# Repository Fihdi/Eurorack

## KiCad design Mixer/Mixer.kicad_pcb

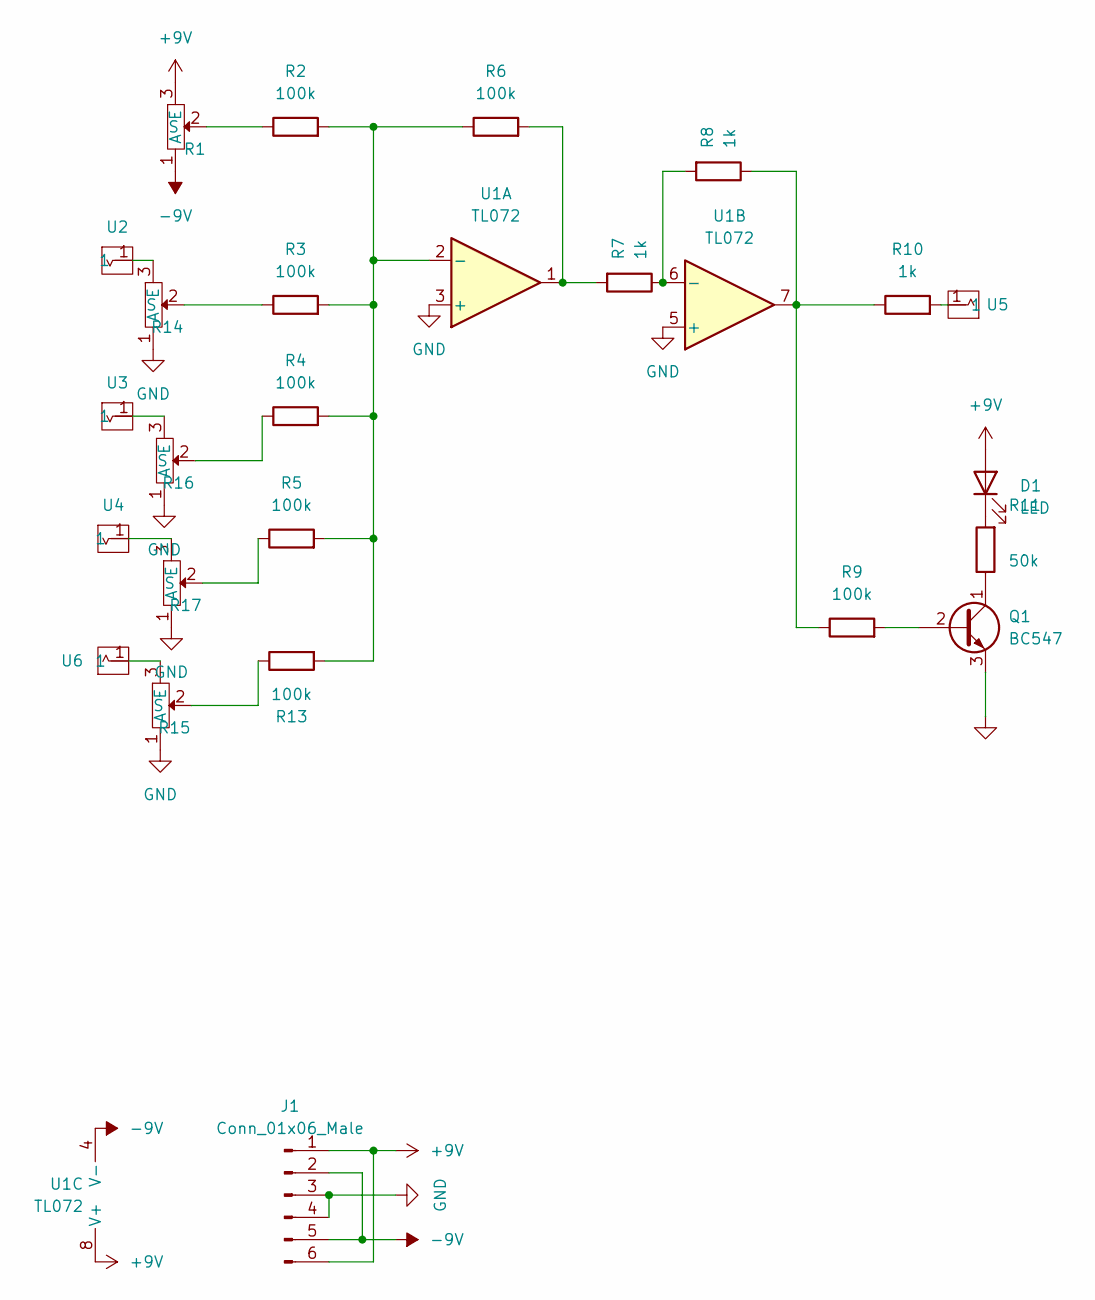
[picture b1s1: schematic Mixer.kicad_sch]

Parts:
D1: LED; LED_D5.0mm
J1: Conn_01x06_Male; PinHeader_1x06_P2.54mm_Vertical
Q1: BC547; TO-92_Inline_Wide
R1, R14, R15, R16, R17: AlpsPot
R2, R3, R4, R5, R6, R9, R13: 100k; R_Axial_DIN0204_L3.6mm_D1.6mm_P7.62mm_Horizontal
R7, R8, R10: 1k; R_Axial_DIN0204_L3.6mm_D1.6mm_P7.62mm_Horizontal
R11: 50k; R_Axial_DIN0204_L3.6mm_D1.6mm_P7.62mm_Horizontal
U1: TL072; DIP-8_W7.62mm
U2, U3, U4, U5, U6: Aux_flush; 3mm5 Mono Aux

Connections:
+9V: D1.2 (A), J1.1, J1.6, R1.3 (E), U1.8 (V+)
-9V: J1.2, J1.5, R1.1 (A), U1.4 (V-)
GND: J1.3, J1.4, Q1.3 (E), R14.1 (A), R15.1 (A), R16.1 (A), R17.1 (A), U1.3 (+), U1.5 (+)
unnamed: D1.1 (K), R11.2
unnamed: Q1.2 (B), R9.2
unnamed: Q1.1 (C), R11.1
unnamed: R1.2 (S), R2.1
unnamed: R6.2, R7.2, U1.1
unnamed: R8.1, R9.1, R10.1, U1.7
unnamed: R10.2, U5.1
unnamed: R14.3 (E), U2.1
unnamed: R3.1, R14.2 (S)
unnamed: R15.3 (E), U6.1
unnamed: R13.1, R15.2 (S)
unnamed: R16.3 (E), U3.1
unnamed: R4.1, R16.2 (S)
unnamed: R17.3 (E), U4.1
unnamed: R5.1, R17.2 (S)
unnamed: R2.2, R3.2, R4.2, R5.2, R6.1, R13.2, U1.2 (-)
unnamed: R7.1, R8.2, U1.6 (-)

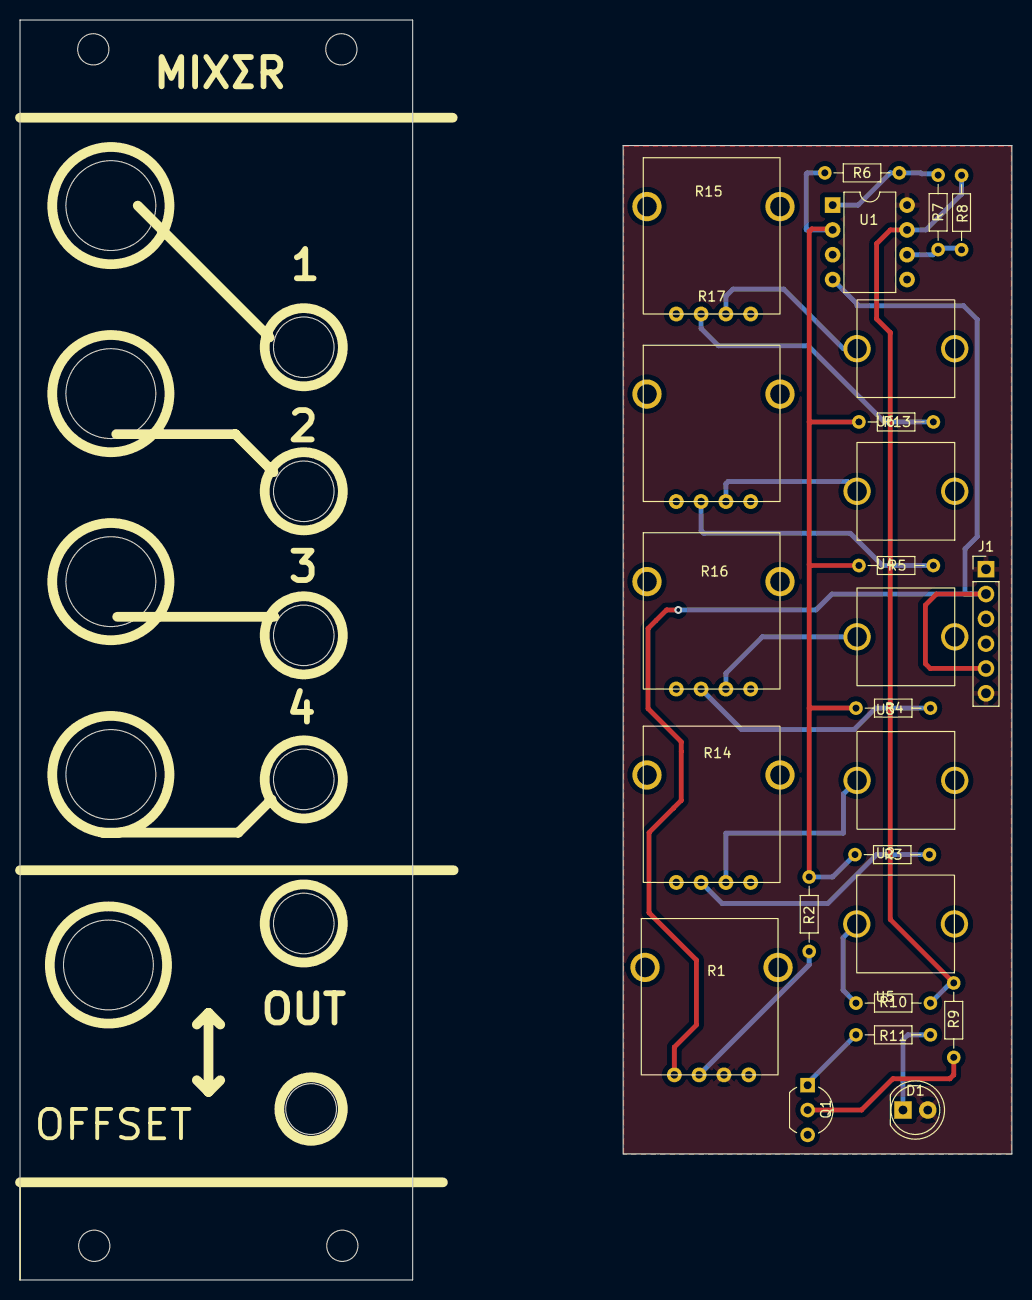
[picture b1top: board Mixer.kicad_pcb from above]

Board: 2 copper layers, 39.8 x 103.2 mm, 25 parts (0 on the bottom side), 20 nets.

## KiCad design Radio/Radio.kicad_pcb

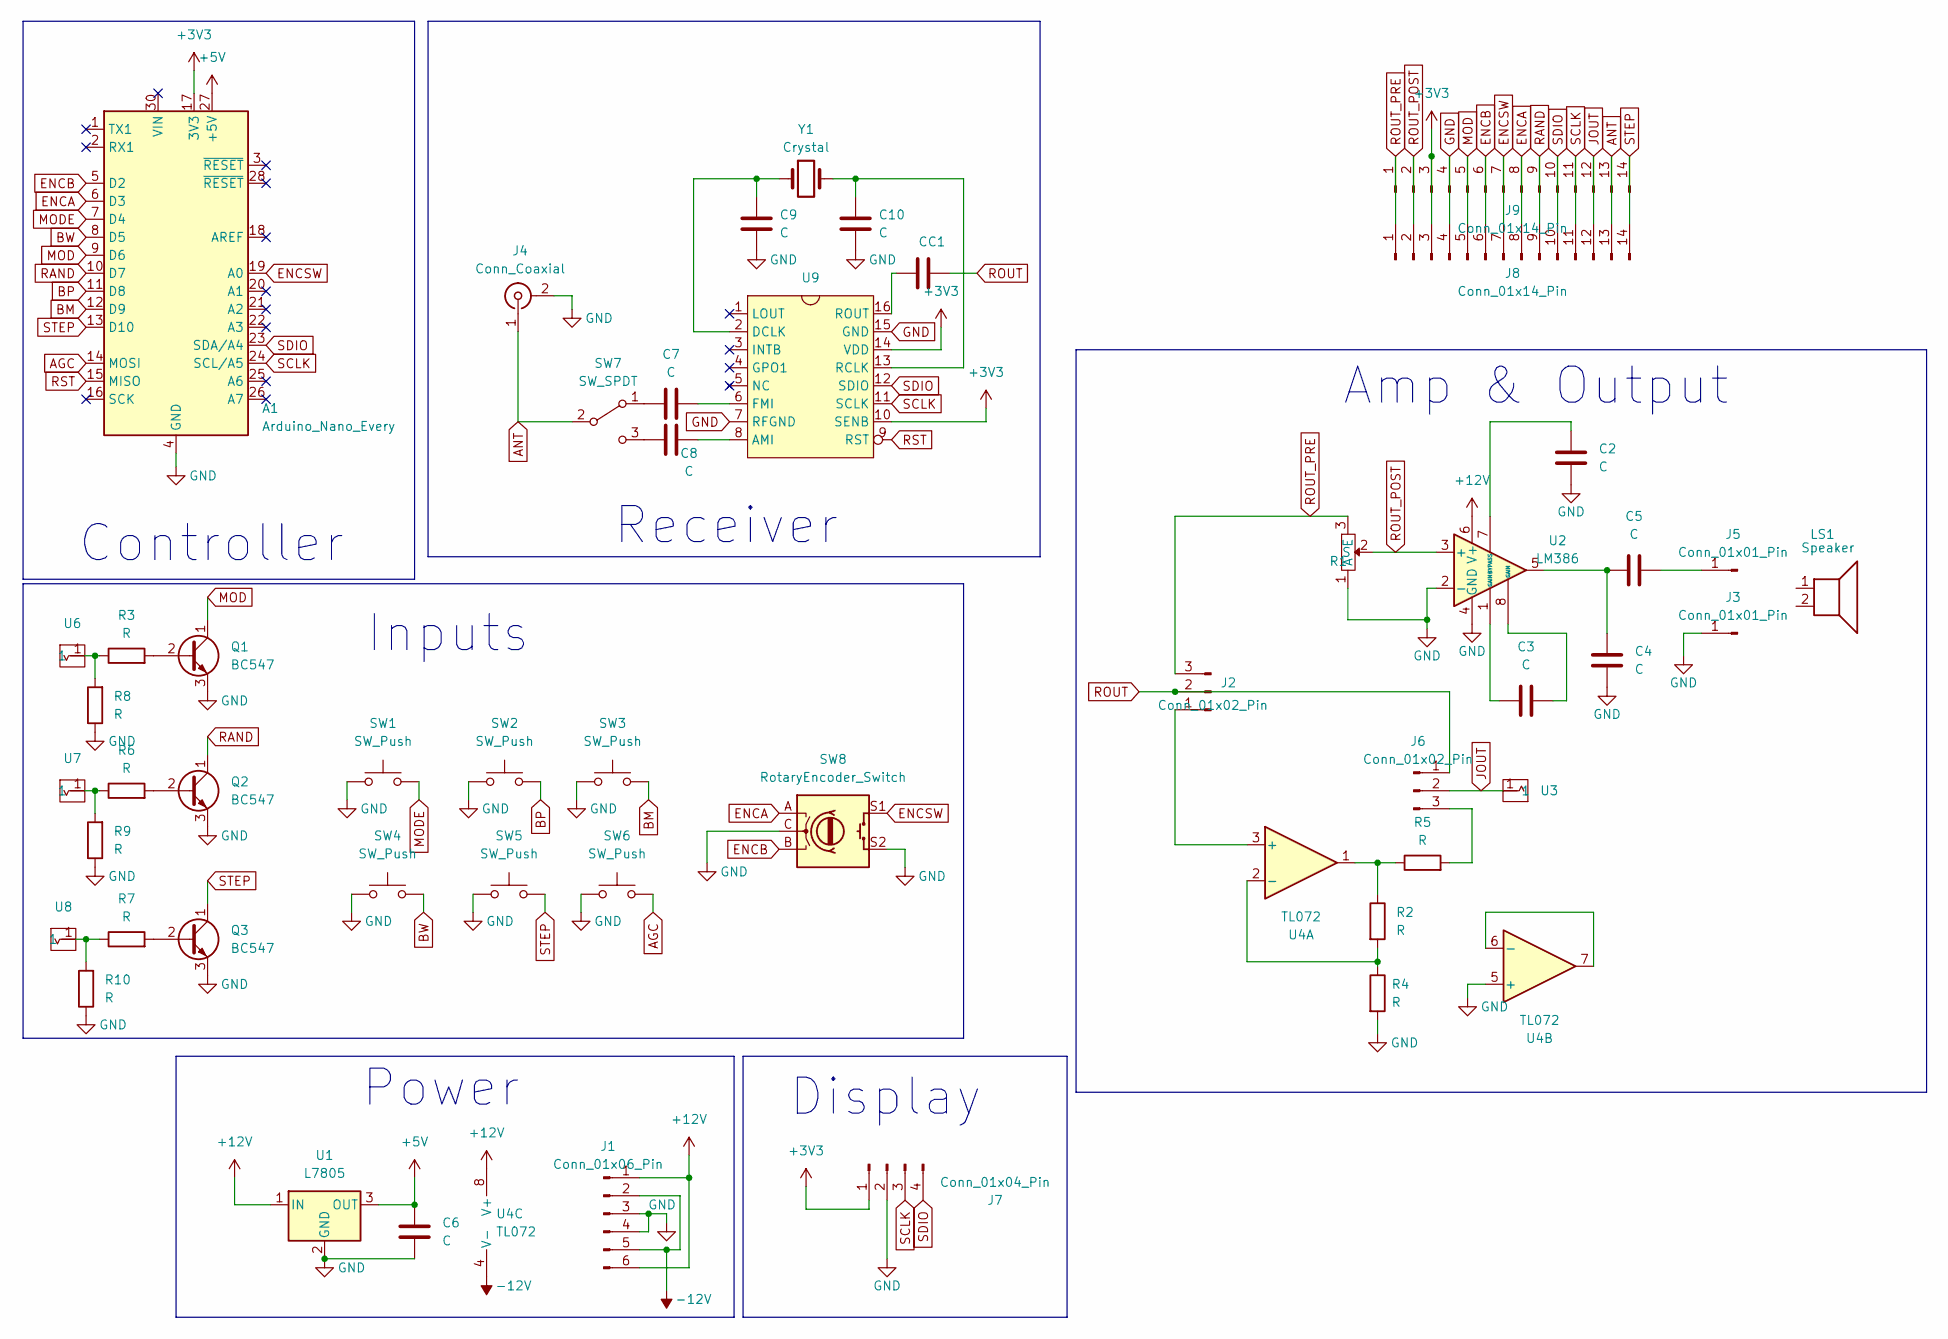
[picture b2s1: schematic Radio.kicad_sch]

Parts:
A1: Arduino_Nano_Every; Arduino_Nano
C1, C2, C3, C4, C5, C6, C7, C8, C9, C10: C; C_Rect_L9.0mm_W2.5mm_P7.50mm_MKT
J1: Conn_01x06_Pin; PinHeader_1x06_P2.54mm_Vertical
J2, J6: Conn_01x02_Pin; PinHeader_1x03_P2.54mm_Vertical
J3, J5: Conn_01x01_Pin; PinSocket_1x01_P2.54mm_Vertical
J4: Conn_Coaxial; BNC_TEConnectivity_1478035_Horizontal
J7: Conn_01x04_Pin; PinSocket_1x04_P2.54mm_Vertical
J8: Conn_01x14_Pin; PinHeader_1x14_P2.54mm_Vertical
J9: Conn_01x14_Pin; PinSocket_1x14_P2.54mm_Vertical
LS1: Speaker
Q1, Q2, Q3: BC547; TO-92_Inline
R1: AlpsPot
R2, R3, R4, R5, R6, R7, R8, R9, R10: R; R_Axial_DIN0204_L3.6mm_D1.6mm_P7.62mm_Horizontal
SW1, SW2, SW3, SW4, SW5, SW6: SW_Push; PinSocket_1x02_P2.54mm_Vertical
SW7: SW_SPDT
SW8: RotaryEncoder_Switch; RotaryEncoder_Alps_EC11E-Switch_Vertical_H20mm
U1: L7805; TO-220-3_Vertical
U2: LM386; DIP-8_W7.62mm
U3, U6, U7, U8: Aux_flush; aux_flush
U4: TL072; DIP-8_W7.62mm
U9: SOIC-16_4.55x10.3mm_P1.27mm
Y1: Crystal; Crystal_DS26_D2.0mm_L6.0mm_Vertical

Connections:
+3V3: A1.17 (3V3), J7.1, J8.3, J9.3, U9.10 (SENB), U9.14 (VDD)
+5V: A1.27 (+5V), C6.1, U1.3 (OUT)
+12V: J1.1, J1.6, U1.1 (IN), U2.6 (V+), U4.8 (V+)
-12V: J1.2, J1.5, U4.4 (V-)
AGC: A1.14 (MOSI), SW6.2
ANT: J4.1 (In), J8.13, J9.13, SW7.2 (B); also elsewhere on the board
BM: A1.12 (D9), SW3.2
BP: A1.11 (D8), SW2.2
BW: A1.8 (D5), SW4.2
ENCA: A1.6 (D3), J8.8, J9.8, SW8.A
ENCB: A1.5 (D2), J8.6, J9.6, SW8.B
ENCSW: A1.19 (A0), J8.7, J9.7, SW8.S1
GND: A1.4 (GND), A1.29 (GND), C2.1, C4.1, C6.2, C9.2, C10.2, J1.3, J1.4, J3.1, J4.2 (Ext), J7.2, J8.4, J9.4, Q1.3 (E), Q2.3 (E), Q3.3 (E), R1.1 (A), R4.2, R8.1, R9.1, R10.1, SW1.1, SW2.1, SW3.1, SW4.1, SW5.1, SW6.1, SW8.C, SW8.S2, U1.2 (GND), U2.2 (-), U2.4 (GND), U4.5 (+), U9.7 (RFGND), U9.15 (GND)
JOUT: J6.2, J8.12, J9.12, U3.1
MOD: A1.9 (D6), J8.5, J9.5, Q1.1 (C)
MODE: A1.7 (D4), SW1.2
unnamed: C3.1, U2.8 (GAIN)
unnamed: C3.2, U2.1 (GAIN)
unnamed: C4.2, C5.2, U2.5
unnamed 19: C7.2, SW7.1 (A); also elsewhere on the board
unnamed 20: C8.2, SW7.3 (C); also elsewhere on the board
unnamed: J2.1, U4.3 (+)
unnamed: C5.1, J5.1
unnamed: J6.3, R5.2
unnamed: Q1.2 (B), R3.2
unnamed: Q2.2 (B), R6.2
unnamed: Q3.2 (B), R7.2
unnamed: R2.1, R5.1, U4.1
unnamed: R3.1, R8.2, U6.1
unnamed: R6.1, R9.2, U7.1
unnamed: R7.1, R10.2, U8.1
unnamed: C2.2, U2.7 (BYPASS)
unnamed: R2.2, R4.1, U4.2 (-)
unnamed: U4.6 (-), U4.7
unnamed: C8.1, U9.8 (AMI)
unnamed: C9.1, U9.2 (DCLK), Y1.1
unnamed: C7.1, U9.6 (FMI)
unnamed: C10.1, U9.13 (RCLK), Y1.2
unnamed: C1.1, U9.16 (ROUT)
RAND: A1.10 (D7), J8.9, J9.9, Q2.1 (C)
ROUT: C1.2, J2.2, J6.1
ROUT_POST: J8.2, J9.2, R1.2 (S), U2.3 (+)
ROUT_PRE: J2.3, J8.1, J9.1, R1.3 (E)
RST: A1.15 (MISO), U9.9 (RST)
SCLK: A1.24 (SCL/A5), J7.3, J8.11, J9.11, U9.11 (SCLK)
SDIO: A1.23 (SDA/A4), J7.4, J8.10, J9.10, U9.12 (SDIO)
STEP: A1.13 (D10), J8.14, J9.14, Q3.1 (C), SW5.2

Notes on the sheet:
Amp & Output
Controller
Power
Display
Inputs
Receiver

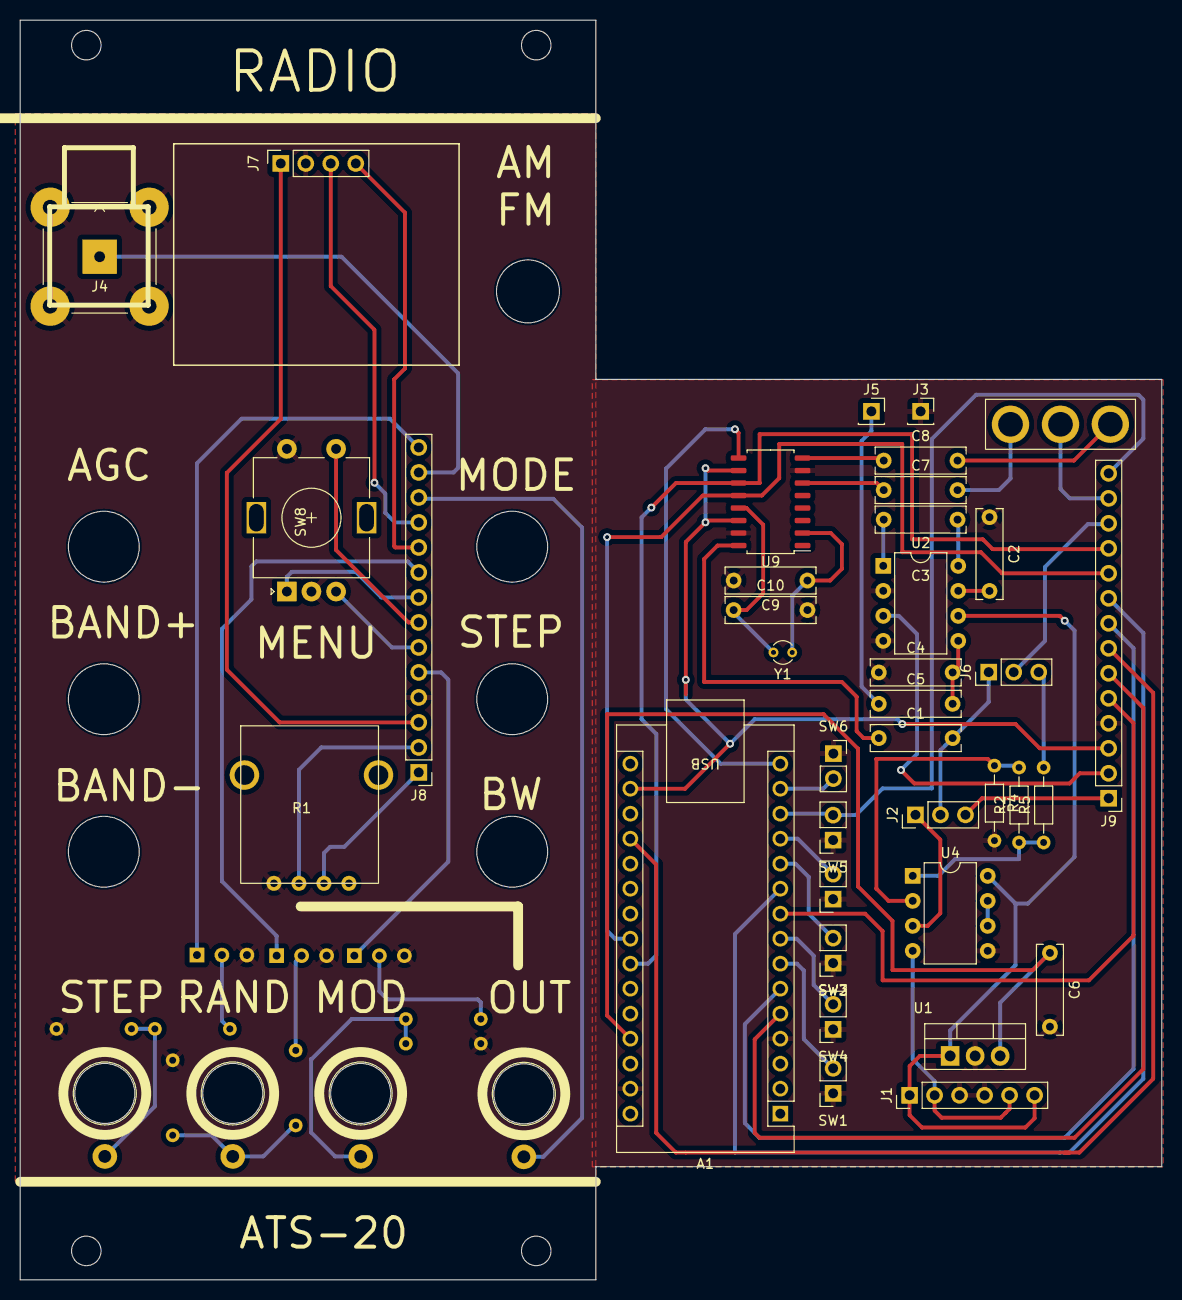
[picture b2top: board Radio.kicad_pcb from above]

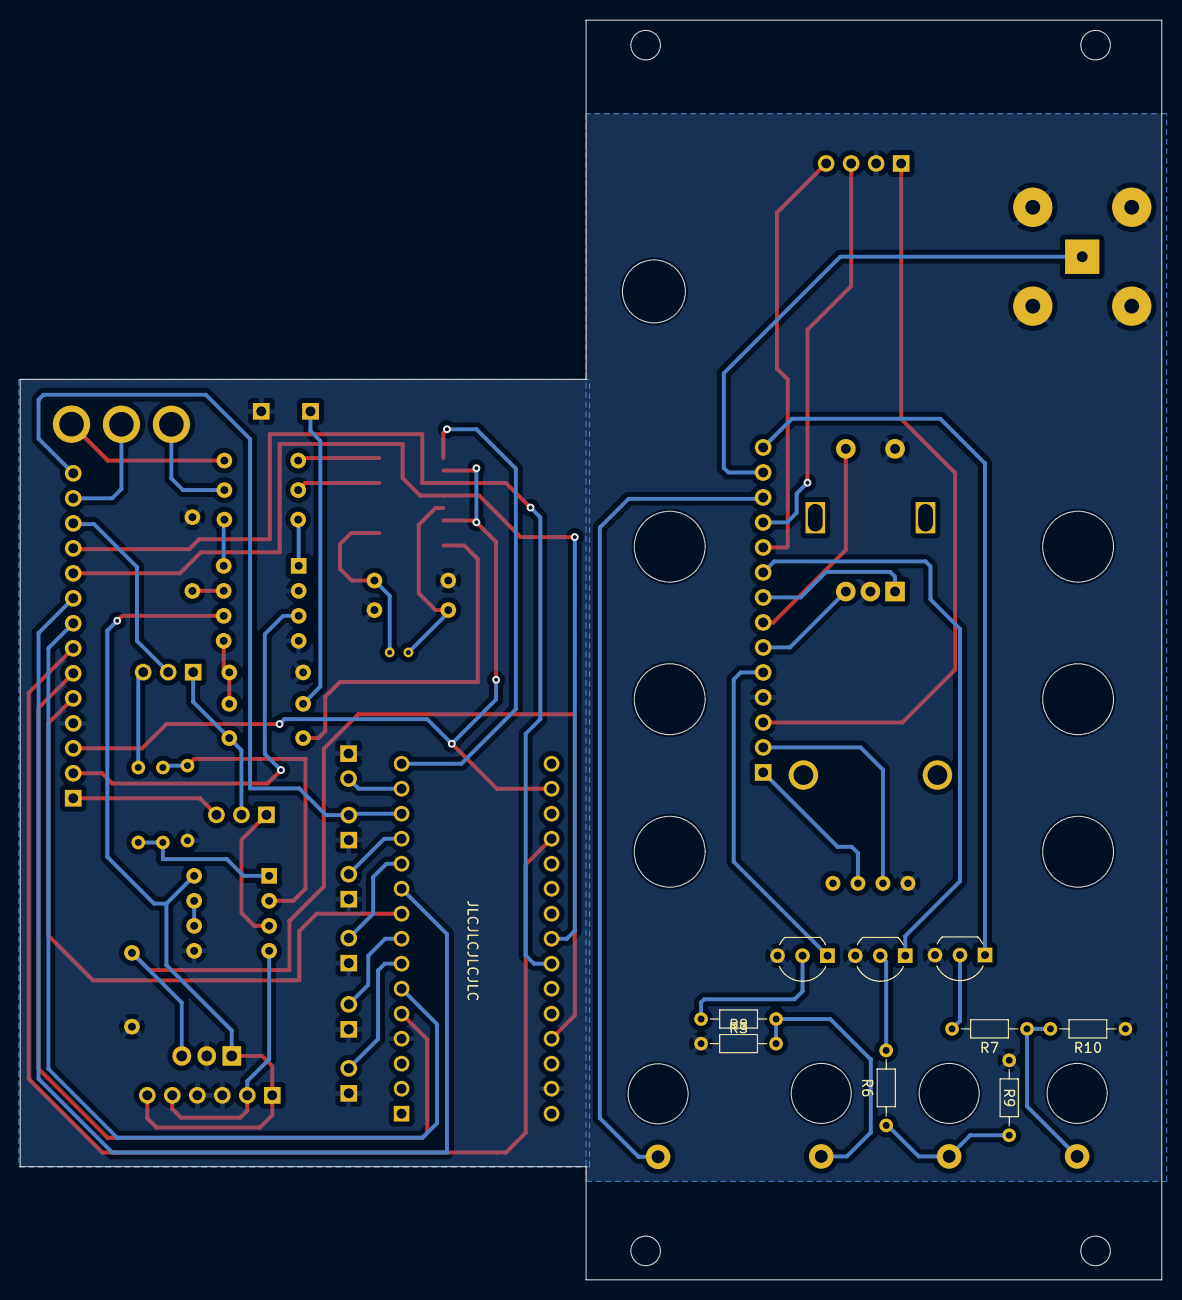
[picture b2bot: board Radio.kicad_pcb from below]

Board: 2 copper layers, 116.0 x 128.0 mm, 50 parts (9 on the bottom side), 47 nets.

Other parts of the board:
U5: Switch

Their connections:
ANT: U5.2; also elsewhere on the board
unnamed 19: U5.1; also elsewhere on the board
unnamed 20: U5.3; also elsewhere on the board

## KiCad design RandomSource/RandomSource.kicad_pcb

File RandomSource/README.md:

# 10hp Sample and Hold / Random Voltage generator 

Improved Version of SAH-TAH, contains a noise generator, sample and hold, burst, slew and bounce circuit. Signal routing is done via switches.  

At its core SAH-TAH has two core components: a noise generator and sample/track and hold. Random also has the same core, but with two extra features, a comparator and a slewing circuit.

SAH/TAH changes the SAH output from sample and hold to track and hold.

The comparator has a reference voltage that can be set with the REF knob. The input to the comparator can be set as NOISE or SAH. When the input signal to the comparator is less than the reference voltage, GATES will output 10V. This can be used to output random gates. BURST doesnt seems to work.

SLEW increases the time it takes for the SLEW OUT output to catch up to the SAH output by varying the RC time constant. The BOUNCE knob adds a delay to the feedback signal with a second RC circuit, causing the SAH SLEW output to over- and undershoot the sampled valued. The MODE switch can select between the first and second RC circuit. This can be used to output smooth random or chaotic random voltages when set to IN/NOISE switch is set to NOISE.

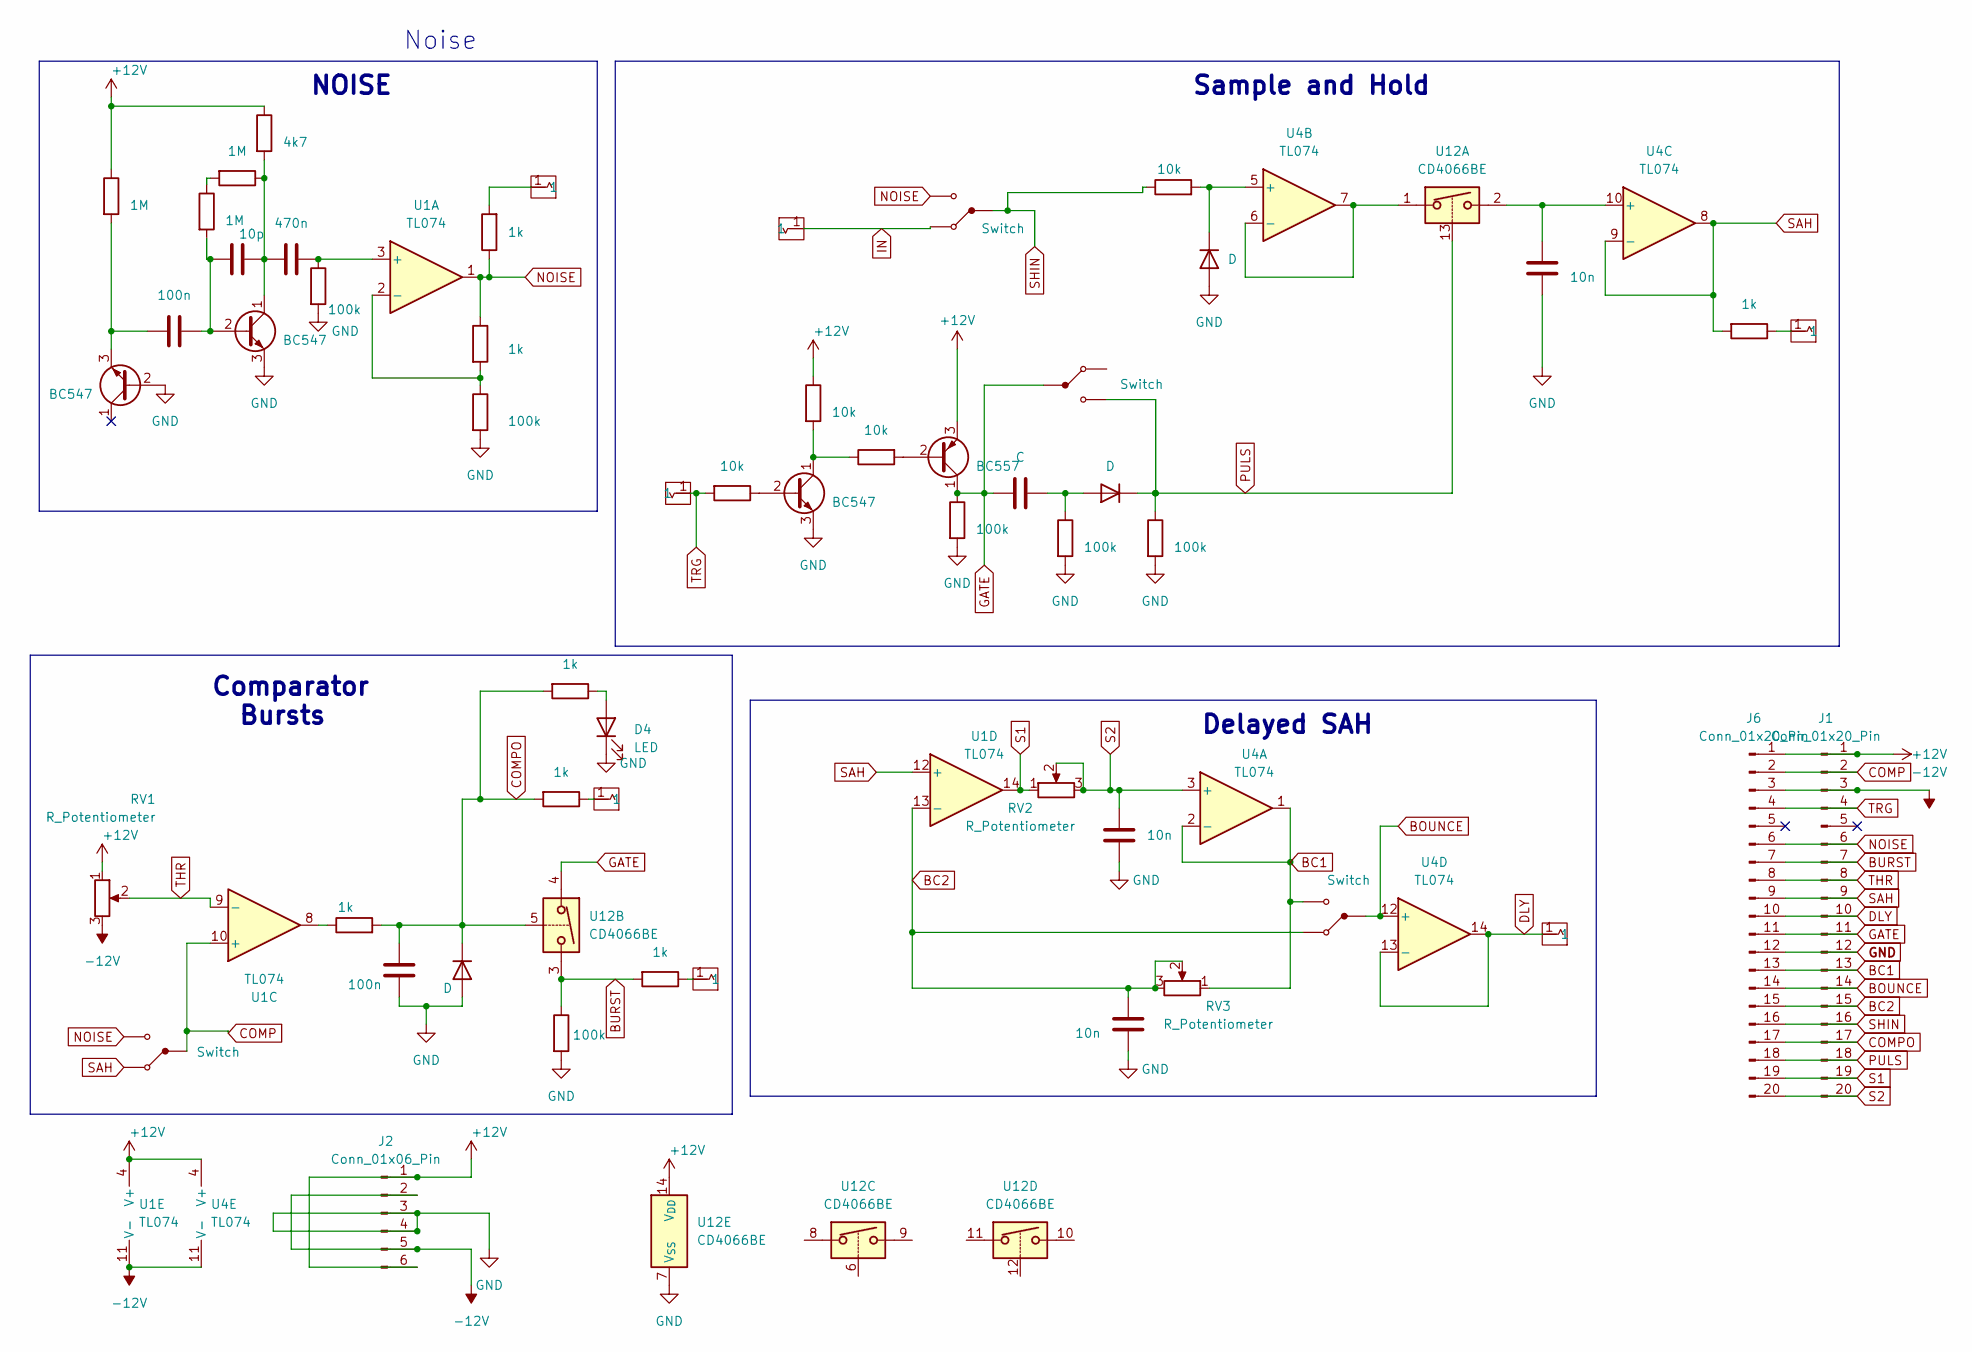
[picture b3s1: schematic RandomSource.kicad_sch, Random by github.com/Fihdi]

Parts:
C1, C8: 100n; C_Axial_L3.8mm_D2.6mm_P7.50mm_Horizontal
C2: 10p; C_Axial_L3.8mm_D2.6mm_P7.50mm_Horizontal
C3: 470n; C_Axial_L3.8mm_D2.6mm_P7.50mm_Horizontal
C4: C; C_Axial_L3.8mm_D2.6mm_P7.50mm_Horizontal
C5, C7: 10n; C_Axial_L3.8mm_D2.6mm_P7.50mm_Horizontal
C6: 10n; C_Axial_L3.8mm_D2.6mm_P10.00mm_Horizontal
D1, D3, D5: D; D_A-405_P5.08mm_Vertical_AnodeUp
D4: LED; LED_D5.0mm
J1, J6: Conn_01x20_Pin; PinSocket_1x20_P2.54mm_Vertical
J2: Conn_01x06_Pin; PinSocket_1x06_P2.54mm_Vertical
Q1, Q2, Q3: BC547; TO-92_Inline_Wide
Q4: BC557; TO-92_Inline_Wide
R1, R2, R3: 1M; R_Axial_DIN0204_L3.6mm_D1.6mm_P7.62mm_Horizontal
R4: 4k7; R_Axial_DIN0204_L3.6mm_D1.6mm_P7.62mm_Horizontal
R5, R7, R10, R11, R12, R17: 100k; R_Axial_DIN0204_L3.6mm_D1.6mm_P7.62mm_Horizontal
R6, R18, R21, R22, R23, R24, R25: 1k; R_Axial_DIN0204_L3.6mm_D1.6mm_P7.62mm_Horizontal
R8, R9, R16, R20: 10k; R_Axial_DIN0204_L3.6mm_D1.6mm_P7.62mm_Horizontal
RV1, RV2, RV3: R_Potentiometer; AlpsPot
U1, U4: TL074; DIP-14_W7.62mm
U2, U6, U9, U10, U11, U13, U14: Aux_flush; 3mm5 Mono Aux
U3, U5, U7, U8: Switch
U12: CD4066BE; DIP-14_W7.62mm

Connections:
+12V: J1.1, J2.1, J2.6, J6.1, Q4.3 (E), R1.1, R4.1, R9.1, RV1.1, U1.4 (V+), U4.4 (V+), U12.14 (V_{DD})
-12V: J1.3, J2.2, J2.5, J6.3, RV1.3, U1.11 (V-), U4.11 (V-)
BC1: J1.13, J6.13, RV3.1, U4.1, U4.2 (-), U7.3
BC2: C7.2, J1.15, J6.15, RV3.2, RV3.3, U1.13 (-), U7.1
BOUNCE: J1.14, J6.14, U4.12 (+), U7.2
BURST: J1.7, J6.7, R17.1, R24.2, U12.3
COMP: J1.2, J6.2, U1.10 (+), U8.2
COMPO: C8.2, D3.1 (K), J1.17, J6.17, R18.2, R23.2, R25.2, U12.5
DLY: J1.10, J6.10, U4.13 (-), U4.14, U11.1
GATE: C4.1, J1.11, J6.11, Q4.1 (C), R10.1, U3.2, U12.4
GND: C5.1, C6.1, C7.1, C8.1, D3.2 (A), D4.1 (K), D5.2 (A), J1.12, J2.3, J2.4, J6.12, Q1.2 (B), Q2.3 (E), Q3.3 (E), R5.2, R7.2, R10.2, R11.2, R12.2, R17.2, U12.7 (V_{SS})
IN: U5.1, U6.1
NOISE: J1.6, J6.6, R6.1, R22.1, U1.1, U5.3, U8.3
unnamed: C4.2, D1.2 (A), R11.1
unnamed: D4.2 (A), R18.1
unnamed: D5.1 (K), R20.2, U4.5 (+)
unnamed: C1.1, Q1.3 (E), R1.2
unnamed: C1.2, C2.1, Q2.2 (B), R2.2
unnamed: C2.2, C3.1, Q2.1 (C), R3.1, R4.2
unnamed: Q3.2 (B), R8.1
unnamed: Q3.1 (C), R9.2, R16.1
unnamed: Q4.2 (B), R16.2
unnamed: R2.1, R3.2
unnamed: R21.1, U13.1
unnamed: R22.2, U14.1
unnamed: R23.1, U10.1
unnamed: R24.1, U9.1
unnamed: R25.1, U1.8
unnamed: C3.2, R5.1, U1.3 (+)
unnamed: R6.2, R7.1, U1.2 (-)
unnamed: U4.6 (-), U4.7, U12.1
unnamed: C5.2, U4.10 (+), U12.2
PULS: D1.1 (K), J1.18, J6.18, R12.1, U3.3, U12.13
S1: J1.19, J6.19, RV2.1, U1.14
S2: C6.2, J1.20, J6.20, RV2.2, RV2.3, U4.3 (+)
SAH: J1.9, J6.9, R21.2, U1.12 (+), U4.8, U4.9 (-), U8.1
SHIN: J1.16, J6.16, R20.1, U5.2
THR: J1.8, J6.8, RV1.2, U1.9 (-)
TRG: J1.4, J6.4, R8.2, U2.1

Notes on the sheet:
Comparator Bursts
NOISE
Delayed SAH
Sample and Hold
Noise

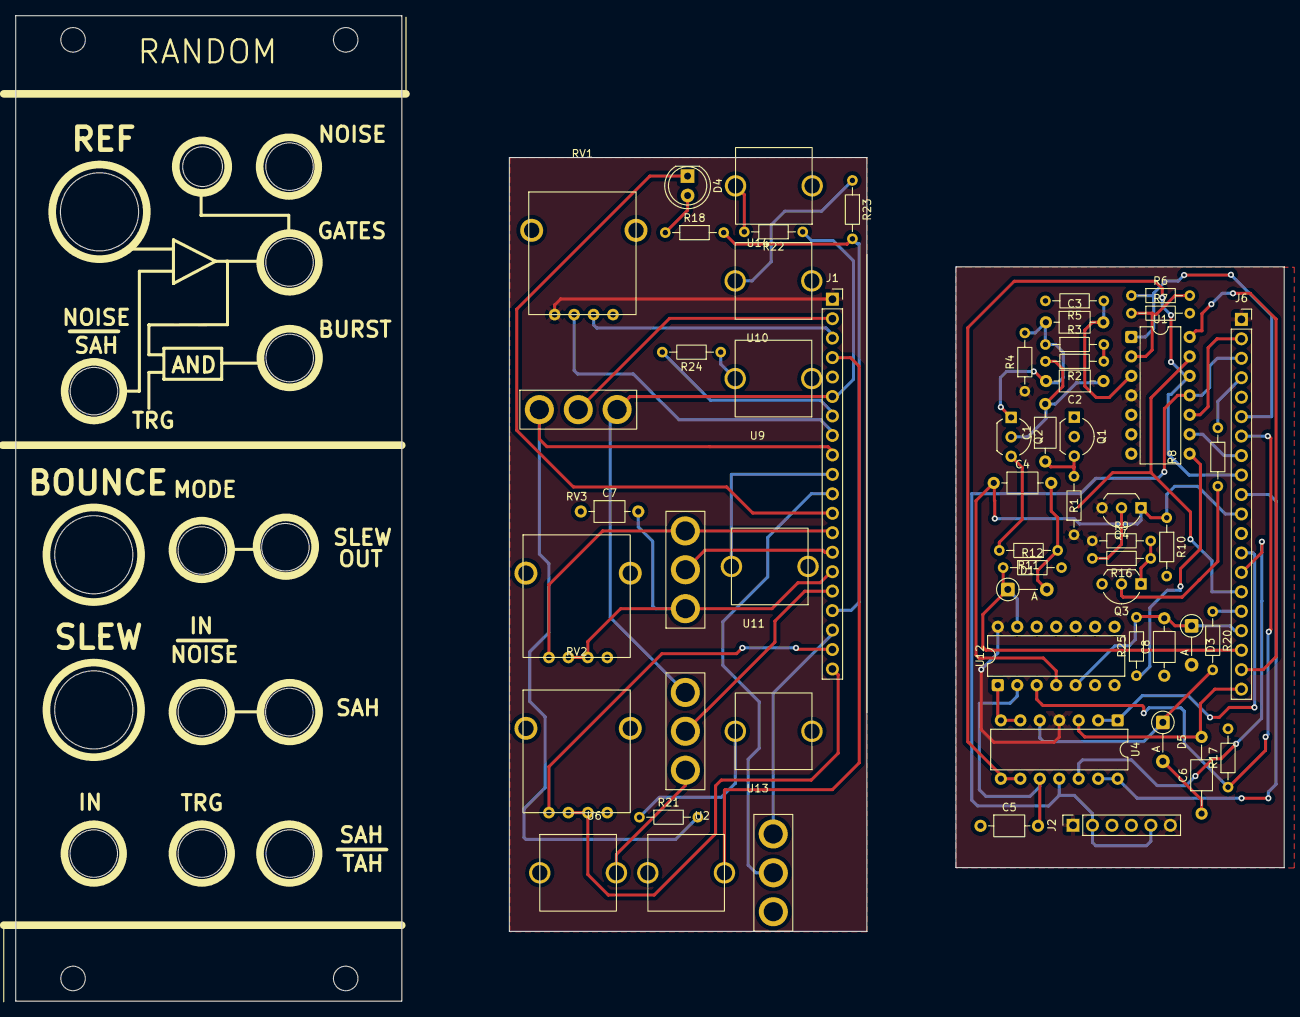
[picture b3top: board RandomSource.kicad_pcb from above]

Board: 2 copper layers, 165.6 x 128.6 mm, 57 parts (0 on the bottom side), 39 nets.

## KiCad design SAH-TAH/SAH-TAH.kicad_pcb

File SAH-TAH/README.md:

Sample and Hold/ Track and Hold module and white Noise

Missing Base resistor for Q4

Opamp needs a high gain because the noise is really small in amplitude.

Hack: Replace the capacitor with a 100K or 10k Pull down Resistor and switch the module to Track and Hold mode. This turns the Sample and hold section into a signal Switch that works with pos. and neg. voltages.

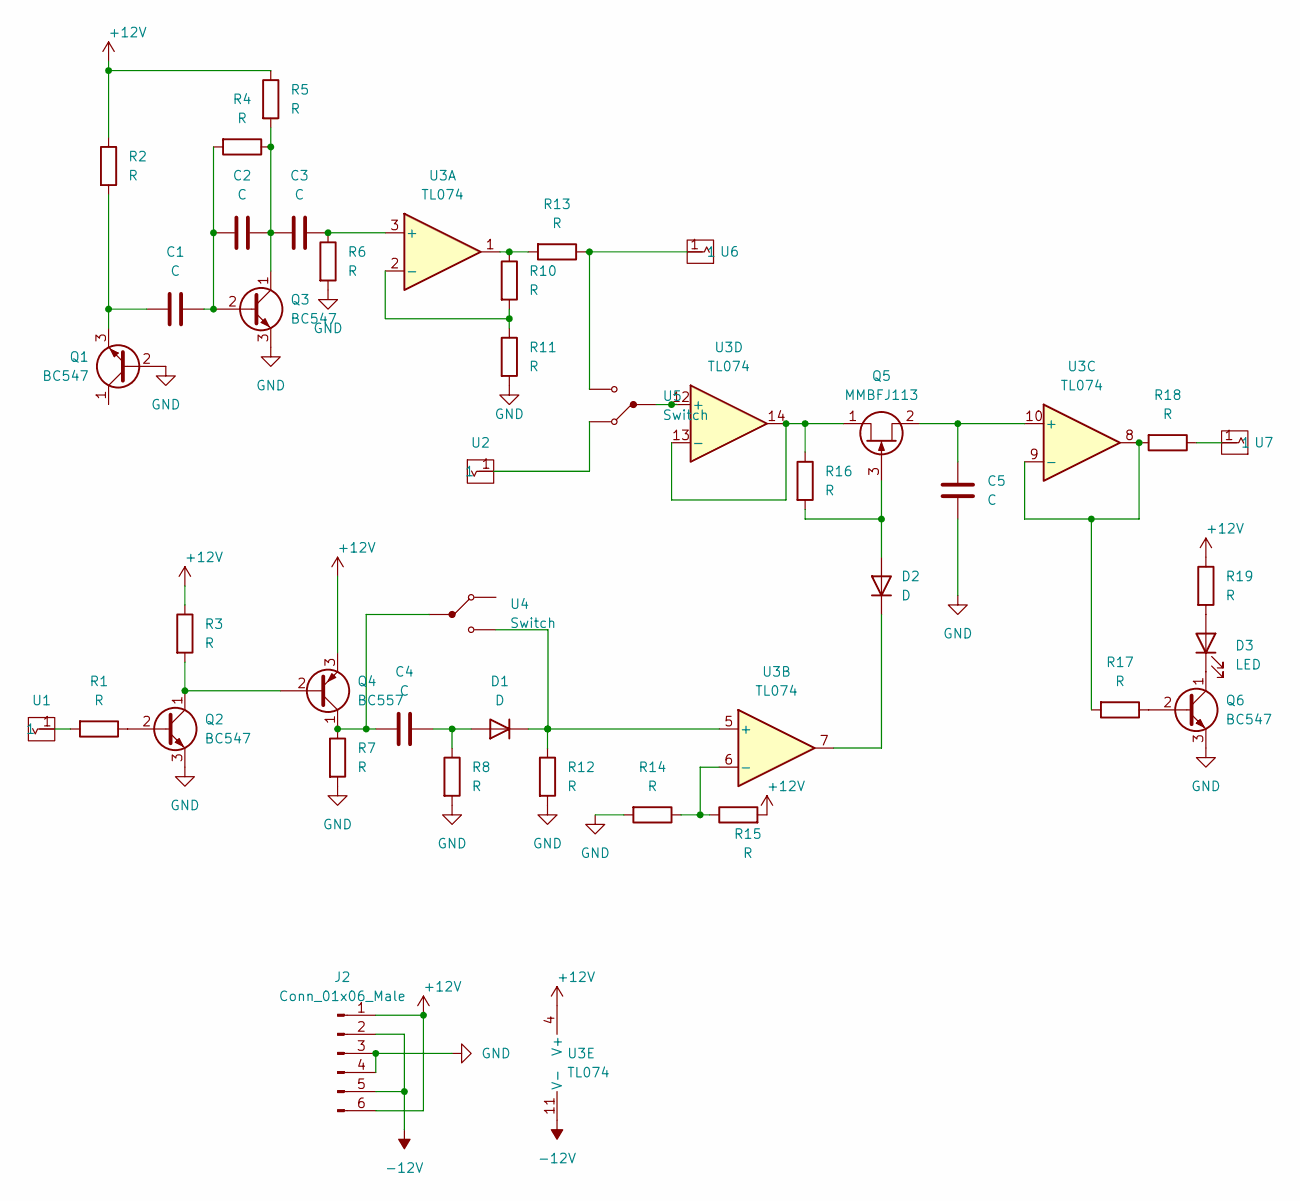
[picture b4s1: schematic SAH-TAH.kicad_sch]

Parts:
C1, C2, C3, C4, C5: C; C_Axial_L3.8mm_D2.6mm_P7.50mm_Horizontal
D1, D2: D; D_A-405_P5.08mm_Vertical_AnodeUp
D3: LED; LED_D5.0mm
J2: Conn_01x06_Male; PinHeader_1x06_P2.54mm_Vertical
Q1, Q2, Q3, Q6: BC547; TO-92_Inline_Wide
Q4: BC557; TO-92_Inline_Wide
Q5: MMBFJ113; TO-92S_Wide
R1, R2, R3, R4, R5, R6, R7, R8, R10, R11, R12, R13, R14, R15, R16, R17, R18, R19: R; R_Axial_DIN0204_L3.6mm_D1.6mm_P7.62mm_Horizontal
U1, U2, U6, U7: Aux_flush; aux_flush
U3: TL074; DIP-14_W7.62mm
U4, U5: Switch

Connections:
+12V: J2.1, J2.6, Q4.3 (E), R2.1, R3.1, R5.1, R15.2, R19.1, U3.4 (V+)
-12V: J2.2, J2.5, U3.11 (V-)
GND: C5.1, J2.3, J2.4, Q1.2 (B), Q2.3 (E), Q3.3 (E), Q6.3 (E), R6.2, R7.2, R8.2, R11.2, R12.2, R14.2
unnamed: C1.1, Q1.3 (E), R2.2
unnamed: C1.2, C2.1, Q3.2 (B), R4.2
unnamed: C2.2, C3.1, Q3.1 (C), R4.1, R5.2
unnamed: C3.2, R6.1, U3.3 (+)
unnamed: C4.1, Q4.1 (C), R7.1, U4.2
unnamed: C4.2, D1.2 (A), R8.1
unnamed: C5.2, Q5.2 (S), U3.10 (+)
unnamed: D1.1 (K), R12.1, U3.5 (+), U4.3
unnamed: D2.1 (K), U3.7
unnamed: D2.2 (A), Q5.3 (G), R16.2
unnamed: D3.1 (K), Q6.1 (C)
unnamed: D3.2 (A), R19.2
unnamed: Q2.1 (C), Q4.2 (B), R3.2
unnamed: Q5.1 (D), R16.1, U3.13 (-), U3.14
unnamed: Q6.2 (B), R17.1
unnamed: Q2.2 (B), R1.1
unnamed: R1.2, U1.1
unnamed: R10.1, R13.2, U3.1
unnamed: R10.2, R11.1, U3.2 (-)
unnamed: R13.1, U5.3, U6.1
unnamed: R14.1, R15.1, U3.6 (-)
unnamed: R17.2, R18.2, U3.8, U3.9 (-)
unnamed: R18.1, U7.1
unnamed: U2.1, U5.1
unnamed: U3.12 (+), U5.2

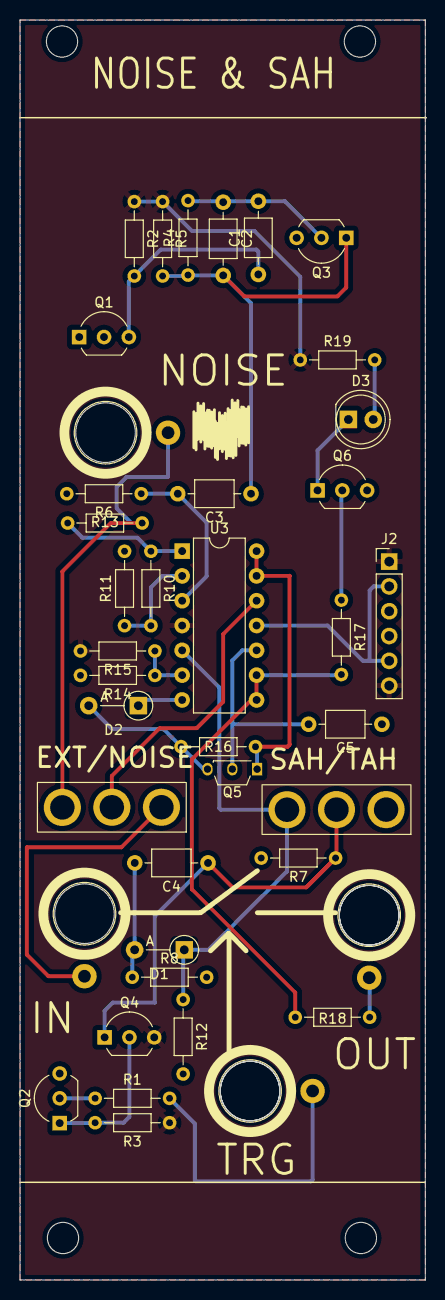
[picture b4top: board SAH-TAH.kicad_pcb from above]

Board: 2 copper layers, 41.5 x 129.0 mm, 40 parts (0 on the bottom side), 28 nets.
